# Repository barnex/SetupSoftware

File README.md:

# SetupSoftware

Software for controlling Dynamat's Magneto-Optical Scanning Microscope.

## Controller
Presents an interface to the STM32 based piezo/magnet controller with 8-channel, 16-bit bipolar ADC input.
Expected port: 5000.

## CurrentSense
An interface to a STM32 based current sensor (current through fast photodiode). 
Expected port: 5002.

## RigolInterface
Interfaces with Rigol multimeter. Expected port: 5005.

## FFTGrabber
Records samples from a soundcard and returns the Fourier transform. Expected port: 5004

Dependencies: 
  * portaudio (Ubuntu 15.04: ``sudo apt-get install portaudio19-dev``)
  * fftw (Ubuntu 15.04: ``sudo apt-get install fftw-dev``)

## HPInterface
Interfaces both with a Prologix or Arduino based GPIB controller hooked up to the HP 8672A signal generator.
Expected port: 5003 for the TX generator (excitation), 5001 for RX (detection).
Arduino-based GPIB controller firmware image: https://github.com/tibal/agipibi.

## HittiteInterface
Presumably talks to Hittite signal generator.

## Moka
java GUI for imaging with the piezo stage.

## FMRScanner
Reads ~/fmr_scanner.ini and performs FMR scan.

## Piezoscanner
Obsolete, replaced by Moka

## PiezoFMR
Obsolete.

## ScannerGUI
Obsolete, replace by Moka

## Libraries
contains certain functions and definitions that are common to all servers and even firmware. It is strongly recommended to use these, and not code your own.
TODO: makefiles

## STM32F-workarea
contains two projects: Controller firmware and CurrentSense firmware

# Protocol definition
Each server will be run by regular user, using a port specified at runtime. Use SSH tunneling for authentication and
security. Public key auth is recommended for automization.

Commands given to a server are always in ASCII, always capital letters. When (multiple) arguments are given, they are seperated by comma's.
For example, the set the position of the piezo stage halfway in each direction, the command will be (given to "Controller"):
SET,POSITION,0.5,0.5,0.5,0.0

To set the HP 8672A to 6.2GHz:
SET,FREQ,6.2e9

Physical values (frequency, current, ...) will always be handled in SI-units. Piezo position and magnet current are limited
between 0 and 1, no unit.

Each server will always reply with two int32_t values. The first holds the exit code, 1/SUCCESS if al went well. The second holds the number of bytes that will 
be returned to the user. If something went wrong, the resulting error code can be looked up in "Libraries/errors.h".
If you do not read all bytes present, they may be present in the input buffer when you read at a later point in time. After
these two bytes come the rest of the data. Returns are binary, not ASCII, unless the ID is requested.

Each server will always reply to the "ID" command with their respective identification string.

*Note: for list of command and parameters, please consult the source of the corresponding server

# Hardware

Design files for the specific electronics used for this projects are summarized in the "Hardware" folder. This may not
always be the latest version.

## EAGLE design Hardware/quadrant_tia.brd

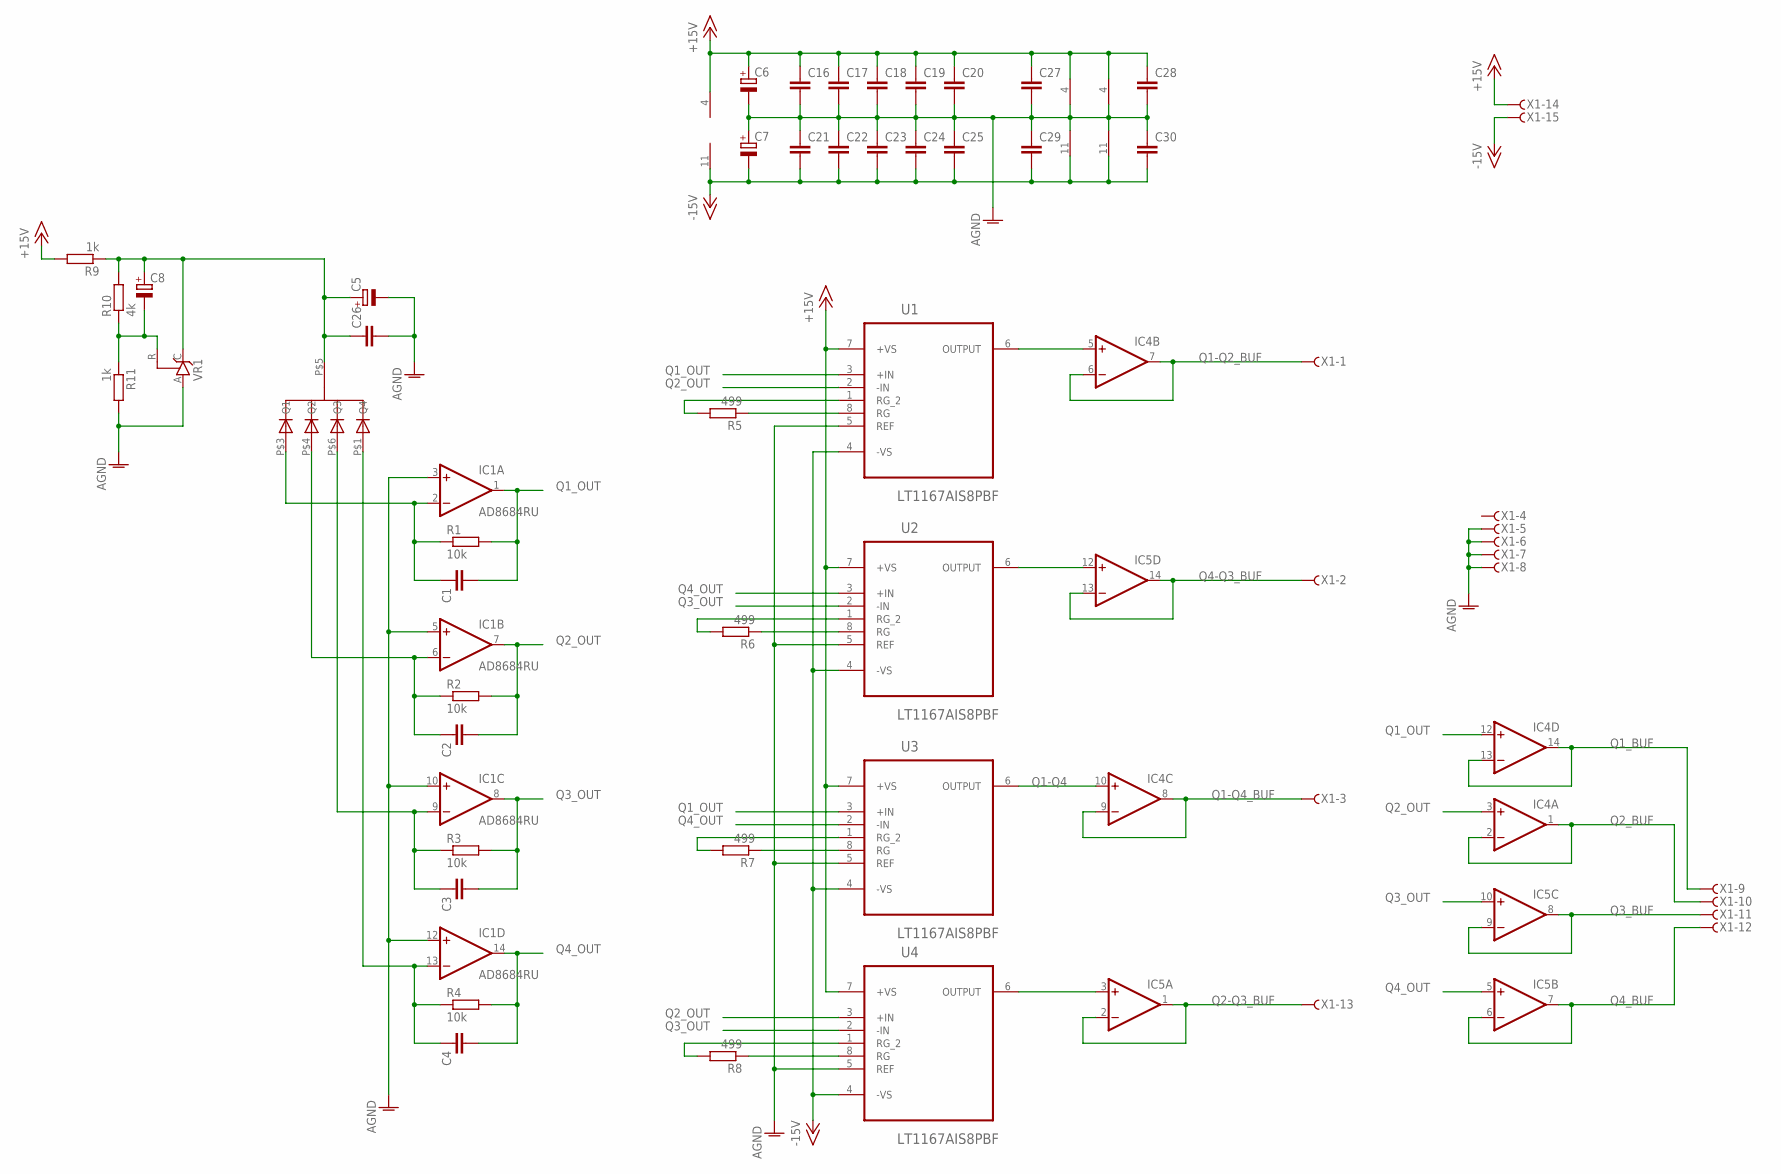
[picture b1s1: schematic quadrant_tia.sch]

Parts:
C1, C2, C3, C4, C16, C17, C18, C19, C20, C21, C22, C23, C24, C25, C26, C27, C28, C29, C30: C-EUC0805K; C0805K
C5, C6, C7, C8: CPOL-EUE5-8.5; E5-8,5
IC1: AD8684RU; TSSOP14
IC4, IC5: 4AMP_P4+11D; SO14
R1, R2, R3, R4: 10k; M1206
R5, R6, R7, R8: 499; M1206
R9, R11: 1k; R0805
R10: 4k; R0805
U1, U2, U3, U4: LT1167AIS8PBF; SOIC127P600X175-8N
U$1: QP50-6; TO-HUGE
VR1: TL431CLP; TO92-CLP
X1: F15HDHS; HDF15H

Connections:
+15V: C6.+, C16.1, C17.1, C18.1, C19.1, C20.1, C27.1, C28.1, IC1.4 (V+), IC4.4 (V+), IC5.4 (V+), R9.2, U1.7 (+VS), U2.7 (+VS), U3.7 (+VS), U4.7 (+VS), X1.14
-15V: C7.-, C21.2, C22.2, C23.2, C24.2, C25.2, C29.2, C30.2, IC1.11 (V-), IC4.11 (V-), IC5.11 (V-), U1.4 (-VS), U2.4 (-VS), U3.4 (-VS), U4.4 (-VS), X1.15
AGND: C5.-, C6.-, C7.+, C16.2, C17.2, C18.2, C19.2, C20.2, C21.1, C22.1, C23.1, C24.1, C25.1, C26.2, C27.2, C28.2, C29.1, C30.1, IC1.3 (+IN), IC1.5 (+IN), IC1.10 (+IN), IC1.12 (+IN), R11.2, U1.5 (REF), U2.5 (REF), U3.5 (REF), U4.5 (REF), VR1.A, X1.5, X1.6, X1.7, X1.8
unnamed: C1.1, IC1.2 (-IN), R1.1, U$1.P$3 (Q1)
unnamed: R7.1, U3.8 (RG)
unnamed: R7.2, U3.1 (RG_2)
unnamed: C2.1, IC1.6 (-IN), R2.1, U$1.P$4 (Q2)
unnamed: R6.1, U2.8 (RG)
unnamed: C3.1, IC1.9 (-IN), R3.1, U$1.P$6 (Q3)
unnamed: R6.2, U2.1 (RG_2)
unnamed: C4.1, IC1.13 (-IN), R4.1, U$1.P$1 (Q4)
unnamed: R5.2, U1.1 (RG_2)
unnamed: R5.1, U1.8 (RG)
unnamed: R8.2, U4.1 (RG_2)
unnamed: R8.1, U4.8 (RG)
unnamed: IC4.5 (+IN), U1.6 (OUTPUT)
unnamed: IC5.3 (+IN), U4.6 (OUTPUT)
unnamed: IC5.12 (+IN), U2.6 (OUTPUT)
unnamed: C5.+, C8.+, C26.1, R9.1, R10.2, U$1.P$5 (C), VR1.C
unnamed: C8.-, R10.1, R11.1, VR1.R
Q1-Q2_BUF: IC4.6 (-IN), IC4.7 (OUT), X1.1
Q1-Q4: IC4.10 (+IN), U3.6 (OUTPUT)
Q1-Q4_BUF: IC4.8 (OUT), IC4.9 (-IN), X1.3
Q1_BUF: IC4.13 (-IN), IC4.14 (OUT), X1.9
Q1_OUT: C1.2, IC1.1 (OUT), IC4.12 (+IN), R1.2, U1.3 (+IN), U3.3 (+IN)
Q2-Q3_BUF: IC5.1 (OUT), IC5.2 (-IN), X1.13
Q2_BUF: IC4.1 (OUT), IC4.2 (-IN), X1.10
Q2_OUT: C2.2, IC1.7 (OUT), IC4.3 (+IN), R2.2, U1.2 (-IN), U4.3 (+IN)
Q3_BUF: IC5.8 (OUT), IC5.9 (-IN), X1.11
Q3_OUT: C3.2, IC1.8 (OUT), IC5.10 (+IN), R3.2, U2.2 (-IN), U4.2 (-IN)
Q4-Q3_BUF: IC5.13 (-IN), IC5.14 (OUT), X1.2
Q4_BUF: IC5.6 (-IN), IC5.7 (OUT), X1.12
Q4_OUT: C4.2, IC1.14 (OUT), IC5.5 (+IN), R4.2, U2.3 (+IN), U3.2 (-IN)

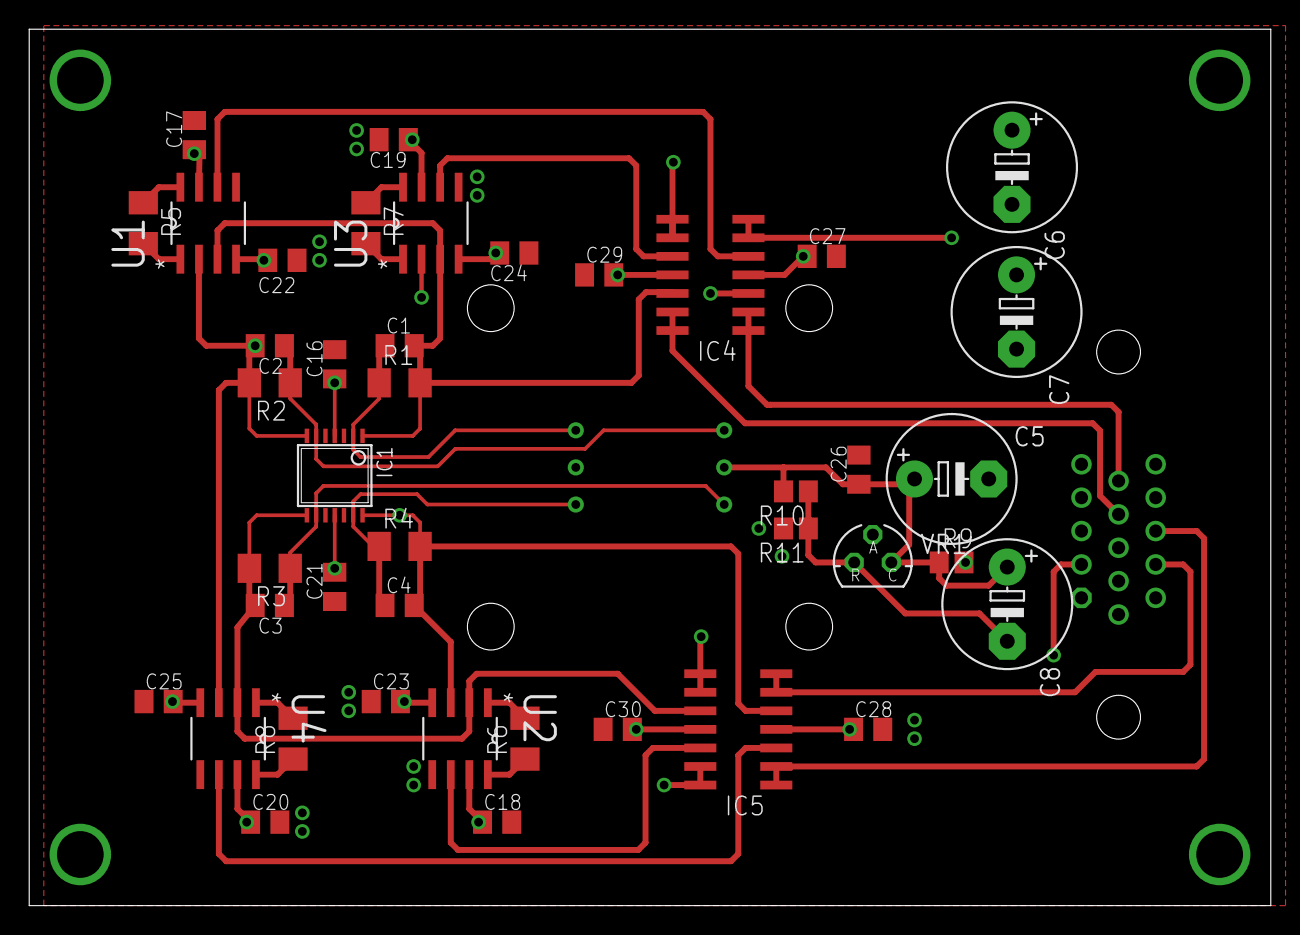
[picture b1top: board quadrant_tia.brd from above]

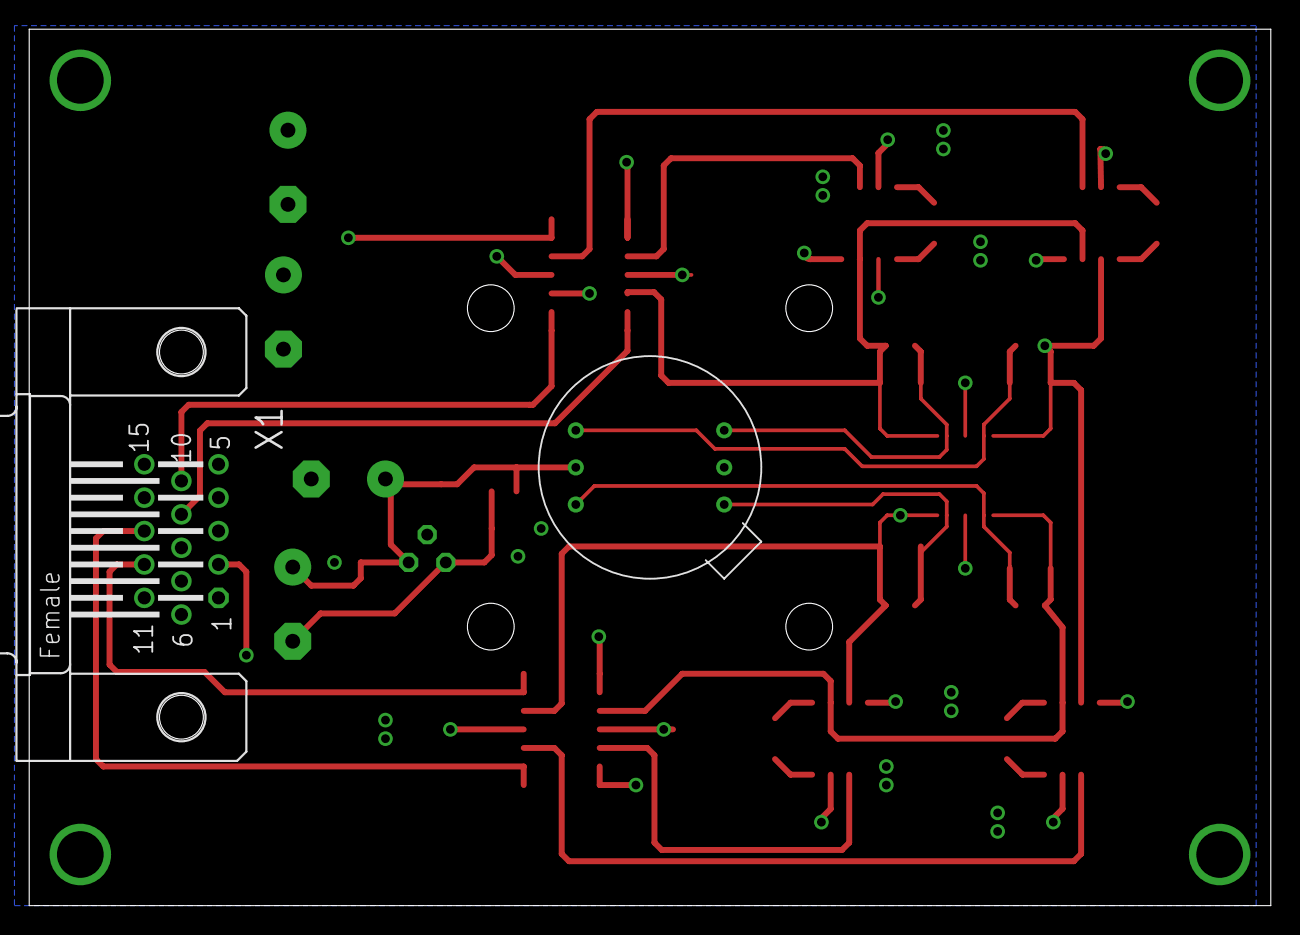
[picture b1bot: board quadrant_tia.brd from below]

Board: 4 copper layers, 85.0 x 60.0 mm, 44 parts (2 on the bottom side), 33 nets.

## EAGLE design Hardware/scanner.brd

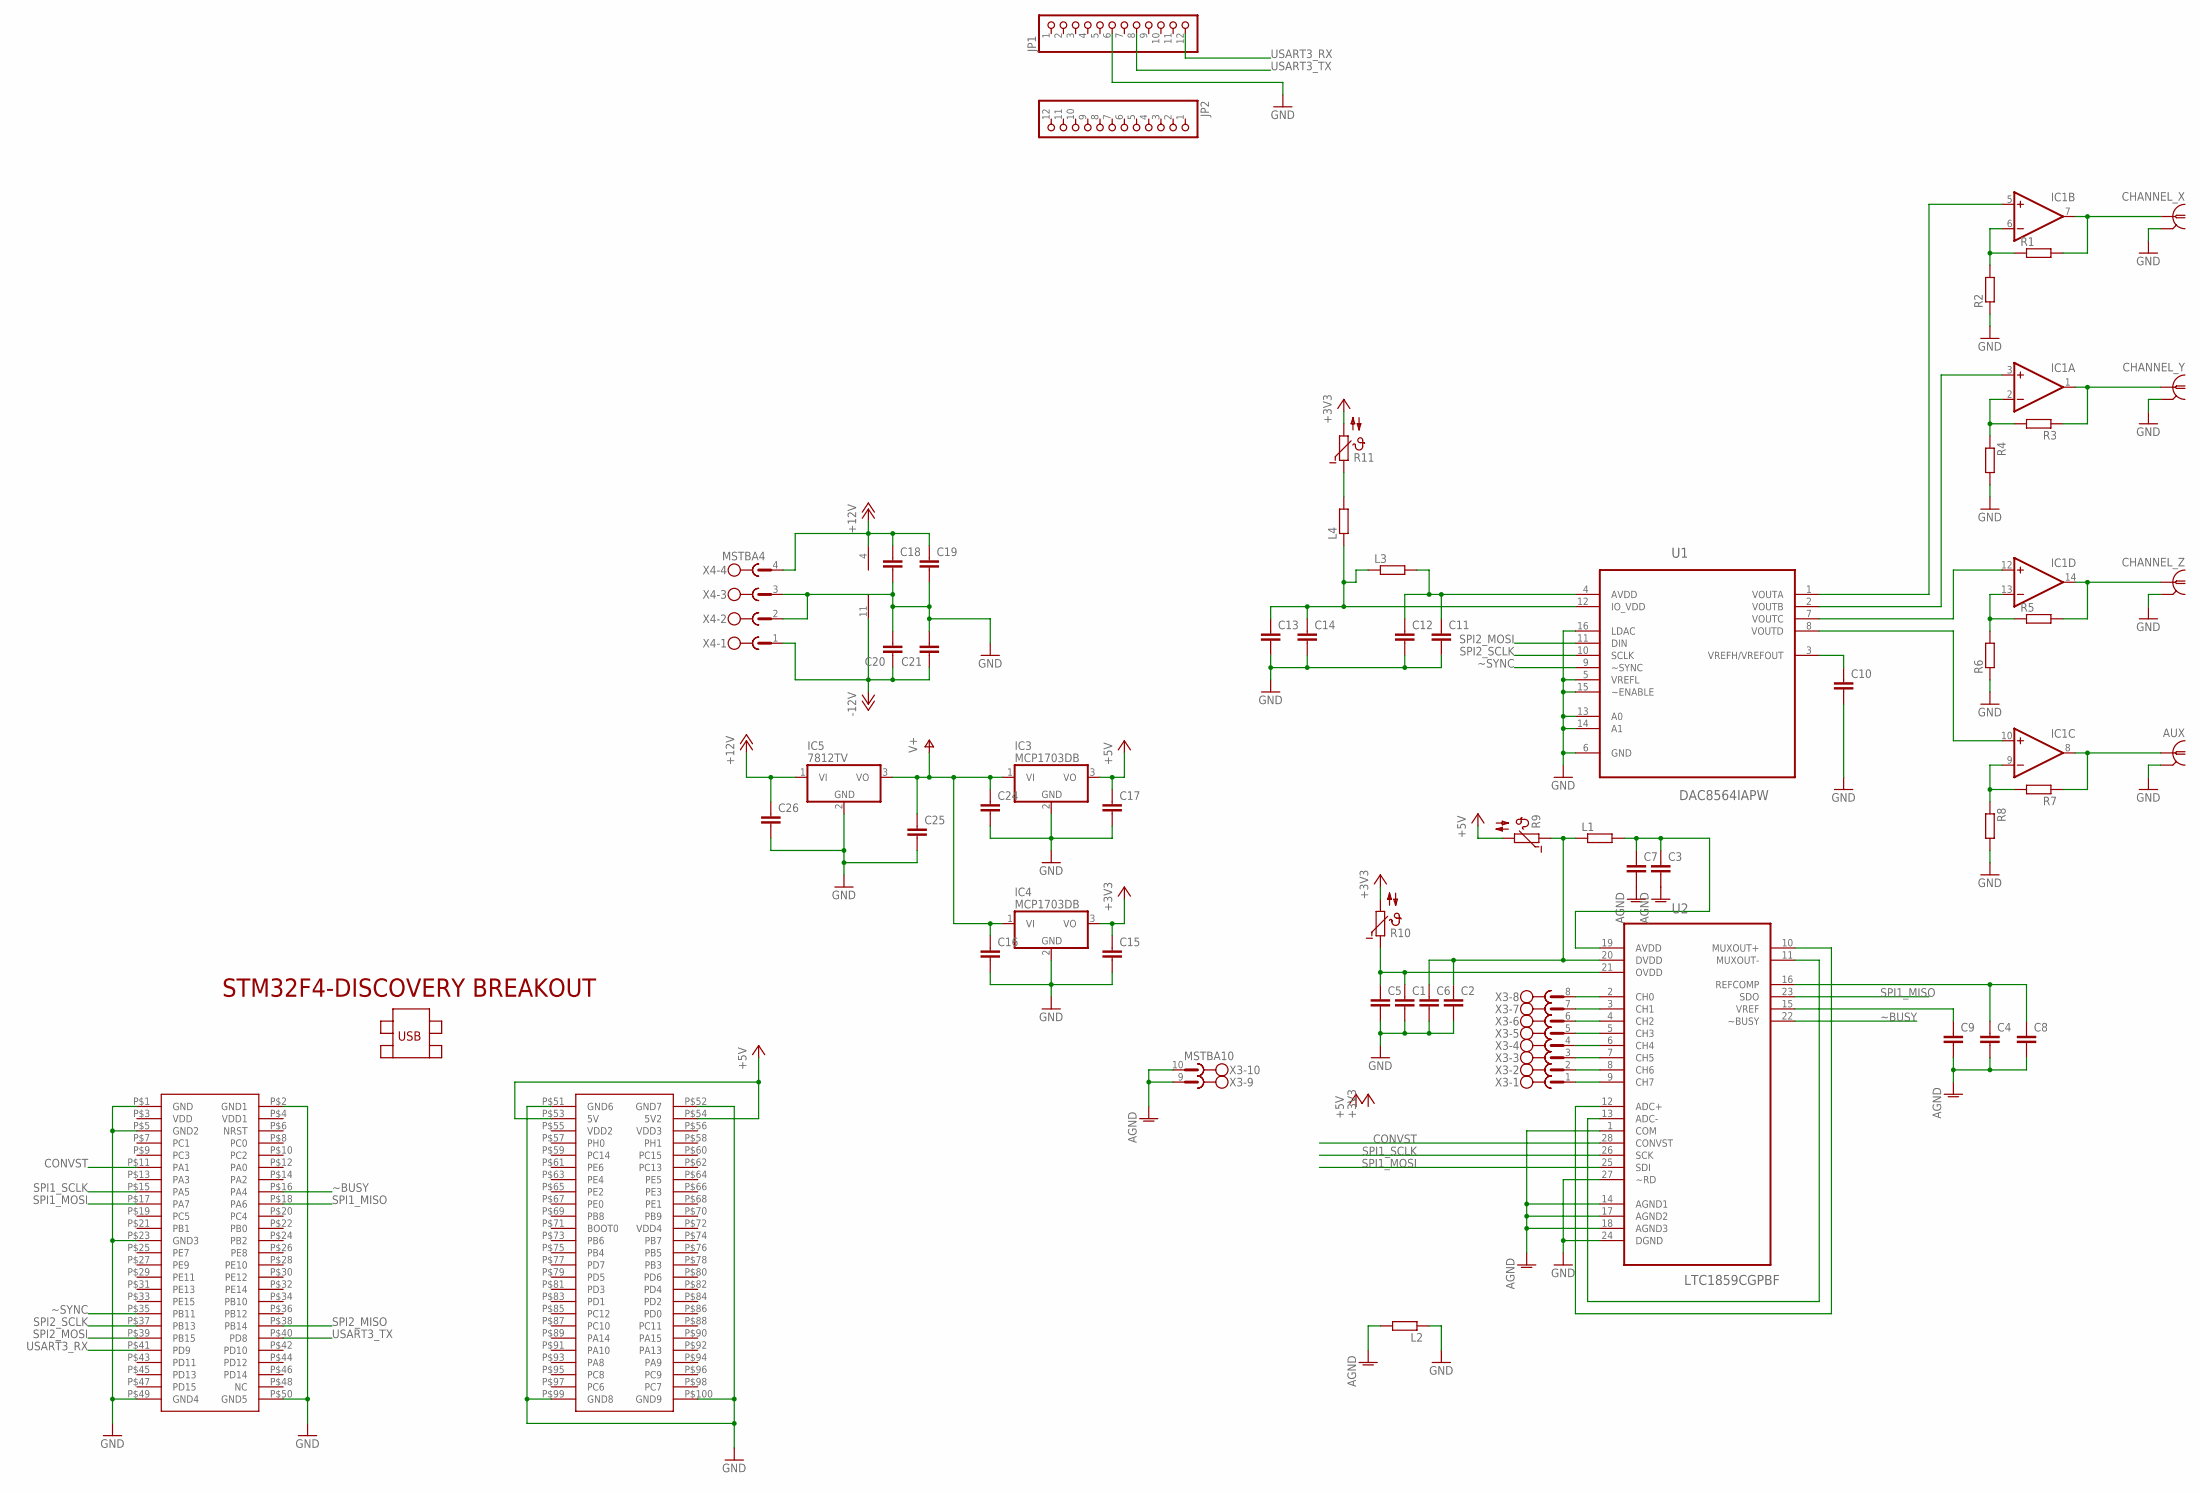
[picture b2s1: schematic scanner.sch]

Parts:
AUX: 1-227161-0; AMP_227161
C1, C2, C3, C4, C10, C11, C14, C15, C16, C17, C19, C21, C24: C-EUC0805; C0805
C5, C6, C7, C8, C9, C12, C13, C18, C20, C25, C26: C-EUC1206; C1206
CHANNEL_X: 1-227161-0; AMP_227161
CHANNEL_Y: 1-227161-0; AMP_227161
CHANNEL_Z: 1-227161-0; AMP_227161
IC1: 4AMP_P4+11D; SO14
IC3, IC4: MCP1703DB; SOT223
IC5: 7812TV; TO220V
JP1, JP2: PINHD-1X12; 1X12
L1, L2, L3, L4: R-EU_M1206; M1206
R1, R2, R3, R4, R5, R6, R7, R8: R-EU_M0805; M0805
R9, R10, R11: NTC644C; N644C
U1: DAC8564IAPW; SOP65P640X120-16N
U2: LTC1859CGPBF; SOP65P780X200-28N
U$2: STM32F4-DISCOVERY
X3: MSTBA10
X4: MSTBA4

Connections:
+3V3: C15.1, IC4.3 (VO), R10.2, R11.2
+5V: C17.1, IC3.3 (VO), R9.2, U$2.P$53 (5V), U$2.P$54 (5V2)
+12V: C18.1, C19.1, C26.1, IC1.4 (V+), IC5.1 (VI), X4.4
-12V: C20.1, C21.1, IC1.11 (V-), X4.1
AGND: C3.2, C4.2, C7.2, C8.2, C9.2, L2.2, U2.1 (COM), U2.14 (AGND1), U2.17 (AGND2), U2.18 (AGND3), X3.9, X3.10
AVCC: C3.1, C7.1, L1.2, U2.19 (AVDD)
CONVST: U2.28 (CONVST), U$2.P$11 (PA1)
GND: AUX.2, C1.2, C2.2, C5.2, C6.2, C10.2, C11.2, C12.2, C13.2, C14.2, C15.2, C16.2, C17.2, C18.2, C19.2, C20.2, C21.2, C24.2, C25.2, C26.2, CHANNEL_X.2, CHANNEL_Y.2, CHANNEL_Z.2, IC3.2 (GND), IC4.2 (GND), IC5.2 (GND), JP1.6, L2.1, R2.1, R4.2, R6.1, R8.2, U1.5 (VREFL), U1.6 (GND), U1.13 (A0), U1.14 (A1), U1.15 (~ENABLE), U1.16 (LDAC), U2.24 (DGND), U2.27 (~RD), U$2.P$1 (GND), U$2.P$2 (GND1), U$2.P$5 (GND2), U$2.P$23 (GND3), U$2.P$49 (GND4), U$2.P$50 (GND5), U$2.P$51 (GND6), U$2.P$52 (GND7), U$2.P$99 (GND8), U$2.P$100 (GND9), X4.2, X4.3
unnamed: U2.10 (MUXOUT+), U2.12 (ADC+)
unnamed: U2.11 (MUXOUT-), U2.13 (ADC-)
unnamed: IC1.5 (+IN), U1.1 (VOUTA)
unnamed: C9.1, U2.15 (VREF)
unnamed: C4.1, C8.1, U2.16 (REFCOMP)
unnamed: U2.3 (CH1), X3.7
unnamed: U2.2 (CH0), X3.8
unnamed: U2.4 (CH2), X3.6
unnamed: U2.5 (CH3), X3.5
unnamed: U2.6 (CH4), X3.4
unnamed: U2.7 (CH5), X3.3
unnamed: U2.8 (CH6), X3.2
unnamed: U2.9 (CH7), X3.1
unnamed: IC1.3 (+IN), U1.2 (VOUTB)
unnamed: IC1.12 (+IN), U1.7 (VOUTC)
unnamed: IC1.10 (+IN), U1.8 (VOUTD)
unnamed: C10.1, U1.3 (VREFH/VREFOUT)
unnamed: CHANNEL_X.1, IC1.7 (OUT), R1.2
unnamed: IC1.6 (-IN), R1.1, R2.2
unnamed: CHANNEL_Y.1, IC1.1 (OUT), R3.1
unnamed: IC1.2 (-IN), R3.2, R4.1
unnamed: C13.1, C14.1, L3.1, L4.1, U1.12 (IO_VDD)
unnamed: CHANNEL_Z.1, IC1.14 (OUT), R5.2
unnamed: IC1.13 (-IN), R5.1, R6.2
unnamed: AUX.1, IC1.8 (OUT), R7.1
unnamed: IC1.9 (-IN), R7.2, R8.1
unnamed: C11.1, C12.1, L3.2, U1.4 (AVDD)
unnamed: L4.2, R11.1
unnamed: C2.1, C6.1, L1.1, R9.1, U2.20 (DVDD)
unnamed: C1.1, C5.1, R10.1, U2.21 (OVDD)
SPI1_MISO: U2.23 (SDO), U$2.P$18 (PA6)
SPI1_MOSI: U2.25 (SDI), U$2.P$17 (PA7)
SPI1_SCLK: U2.26 (SCK), U$2.P$15 (PA5)
SPI2_MISO: U$2.P$38 (PB14)
SPI2_MOSI: U1.11 (DIN), U$2.P$39 (PB15)
SPI2_SCLK: U1.10 (SCLK), U$2.P$37 (PB13)
USART3_RX: JP1.12, U$2.P$41 (PD9)
USART3_TX: JP1.8, U$2.P$40 (PD8)
V+: C16.1, C24.1, C25.1, IC3.1 (VI), IC4.1 (VI), IC5.3 (VO)
~BUSY: U2.22 (~BUSY), U$2.P$16 (PA4)
~SYNC: U1.9 (~SYNC), U$2.P$35 (PB11)

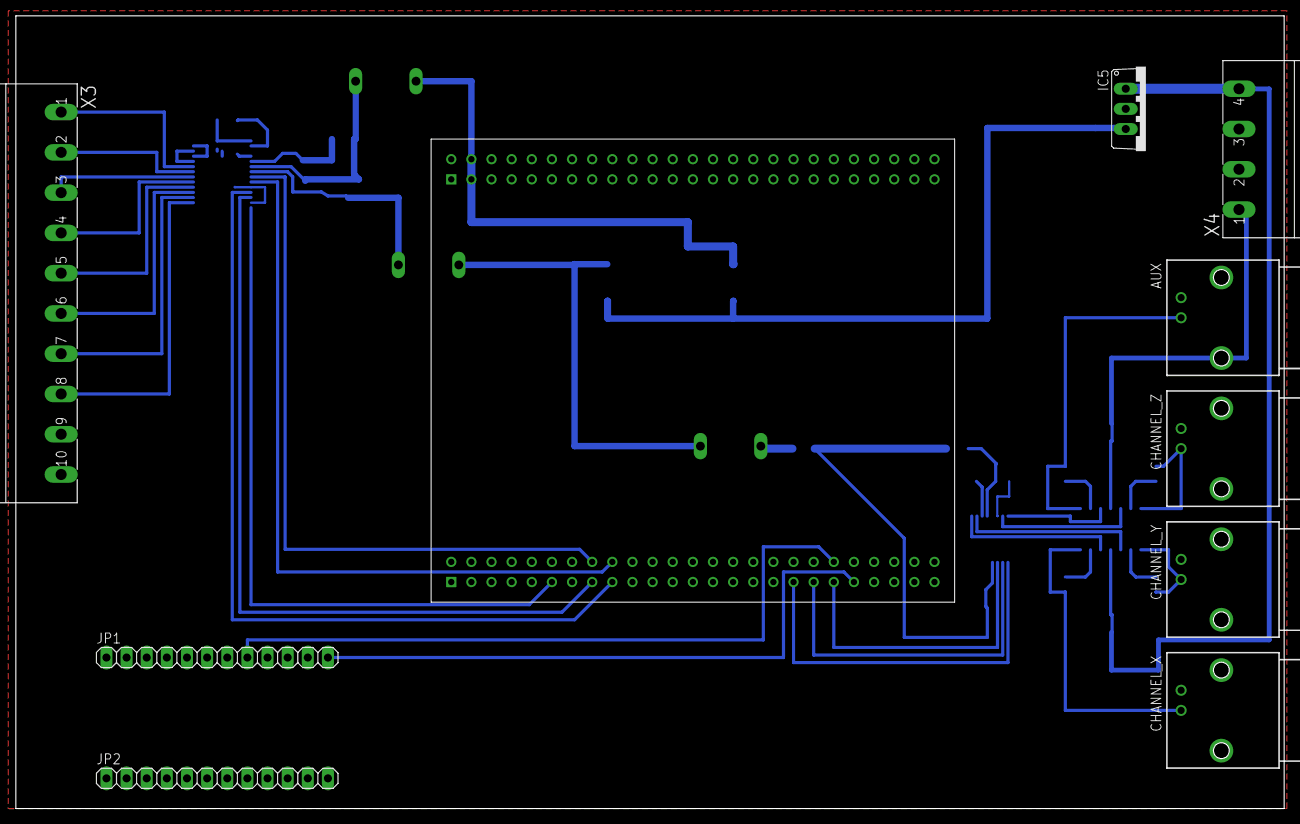
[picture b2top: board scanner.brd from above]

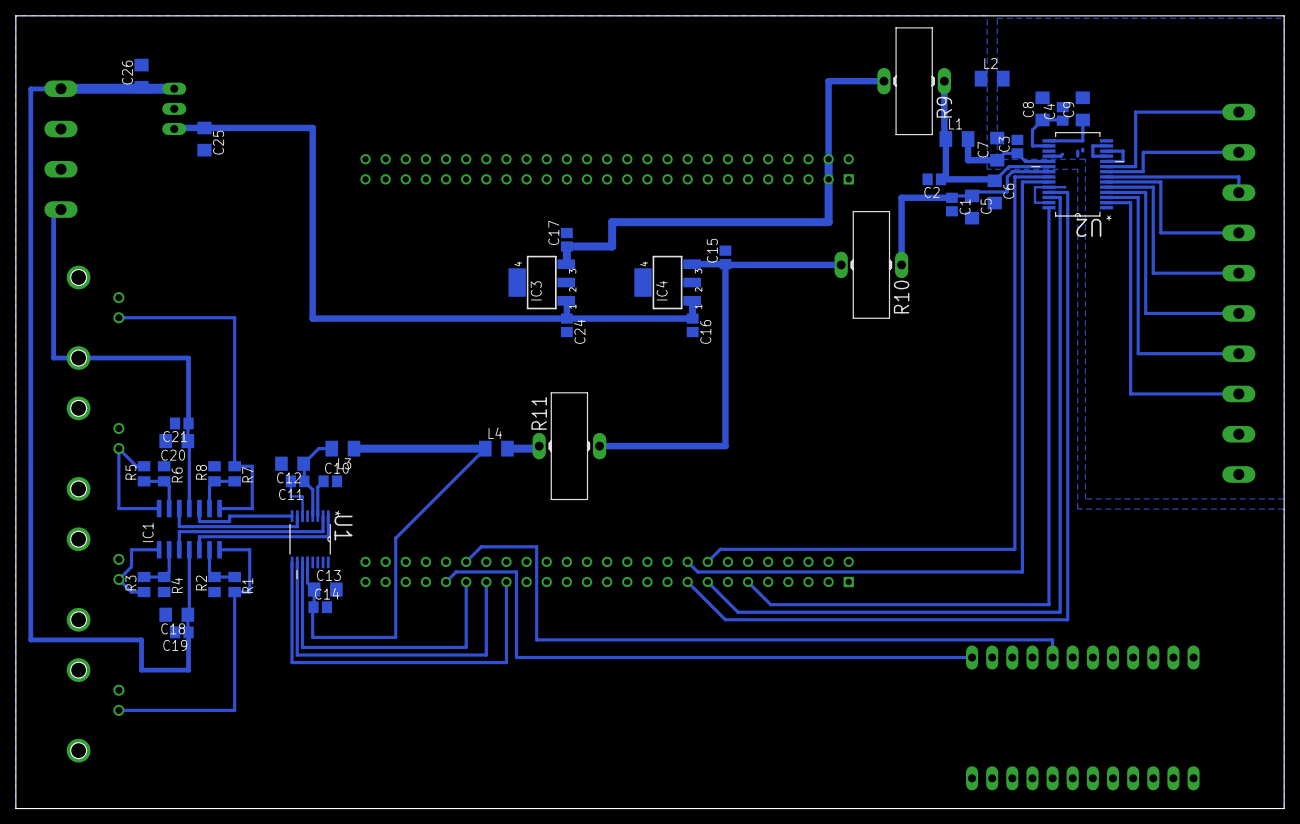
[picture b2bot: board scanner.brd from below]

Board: 2 copper layers, 160.0 x 100.0 mm, 54 parts (44 on the bottom side), 48 nets.

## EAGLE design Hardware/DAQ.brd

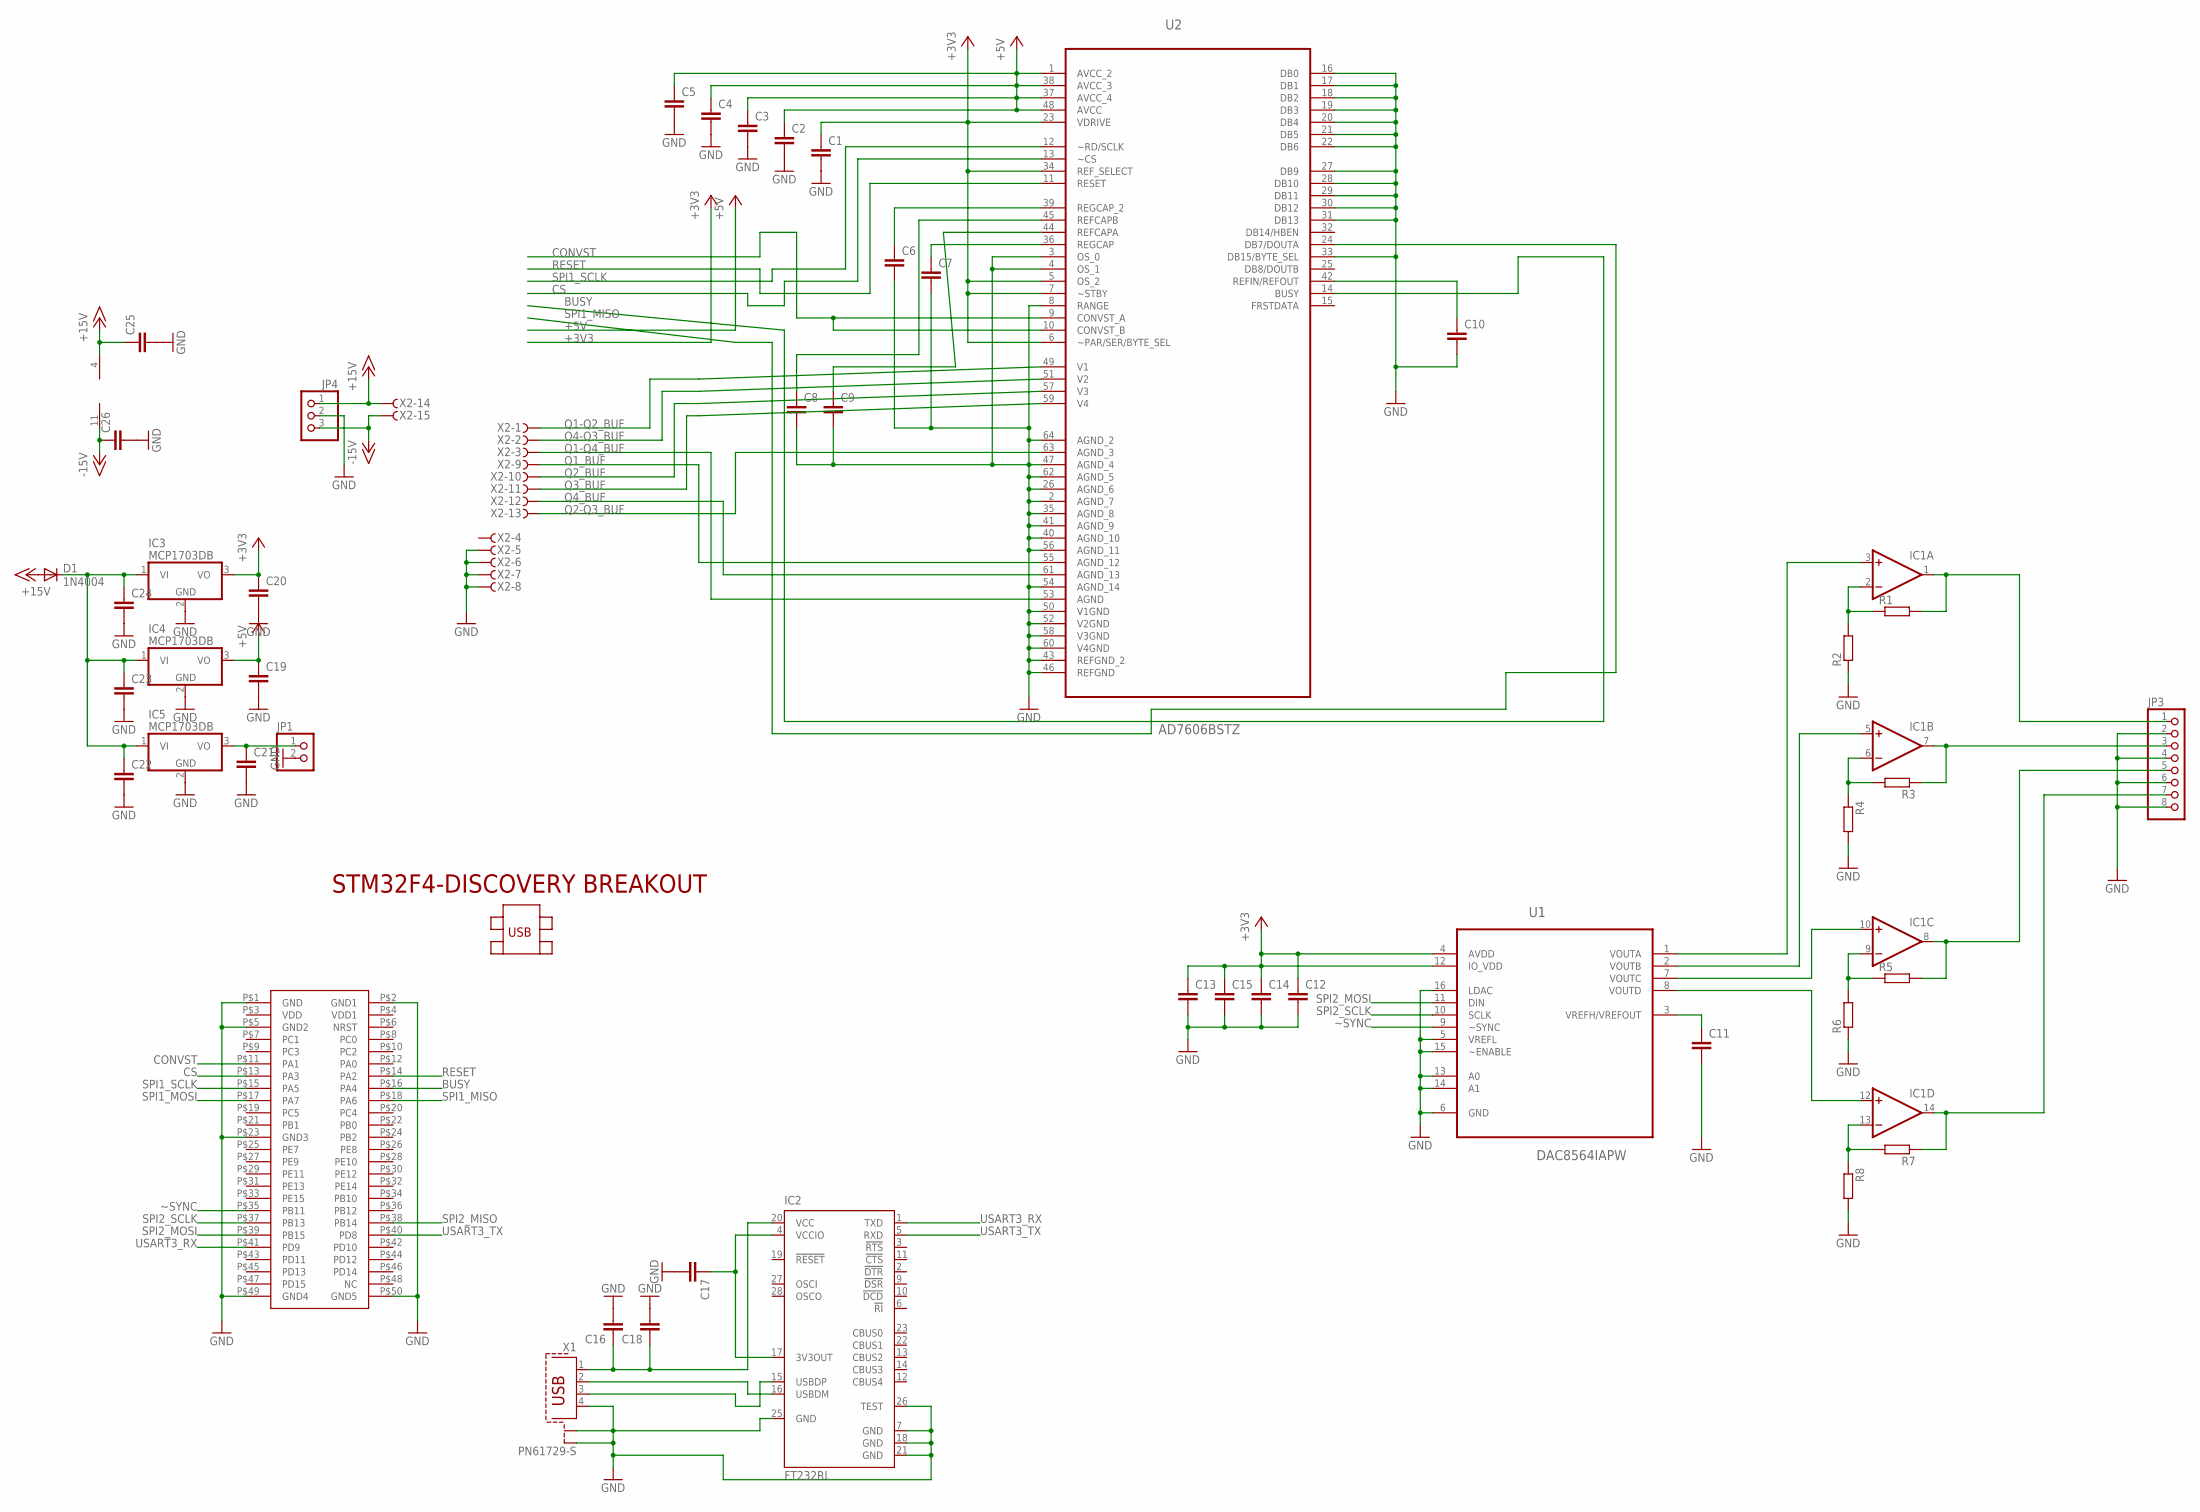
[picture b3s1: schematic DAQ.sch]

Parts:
C1, C2, C3, C4, C5, C6, C7, C11, C12, C13, C14, C15, C16, C17, C18: C-EUC0805; C0805
C8, C9, C10, C19, C20, C21, C22, C23, C24, C25, C26: C-EUC0805K; C0805K
D1: 1N4004; DO41-10
IC1: 4AMP_P4+11D; SO14
IC2: FT232RL; SSOP28
IC3, IC4, IC5: MCP1703DB; SOT223
JP1: PINHD-1X2; 1X02
JP3: PINHD-1X8; 1X08
JP4: PINHD-1X3; 1X03
R1, R2, R3, R4, R5, R6, R7, R8: R-EU_M0805; M0805
U1: DAC8564IAPW; SOP65P640X120-16N
U2: AD7606BSTZ; QFP50P1200X1200X160-64N
U$1: STM32F4-DISCOVERY
X1: PN61729-S
X2: F15HDHS; HDF15H

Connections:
+3V3: C1.1, C12.1, C13.1, C14.1, C15.1, C20.1, IC3.3 (VO), U1.4 (AVDD), U1.12 (IO_VDD), U2.5 (OS_2), U2.6 (~PAR/SER/BYTE_SEL), U2.7 (~STBY), U2.23 (VDRIVE), U2.34 (REF_SELECT)
+5V: C2.1, C3.1, C4.1, C5.1, C19.1, IC4.3 (VO), U2.1 (AVCC_2), U2.37 (AVCC_4), U2.38 (AVCC_3), U2.48 (AVCC)
+15V: C25.1, D1.A, IC1.4 (V+), JP4.1, X2.14
-15V: C26.1, IC1.11 (V-), JP4.3, X2.15
BUSY: U2.14 (BUSY), U$1.P$16 (PA4)
CONVST: U2.9 (CONVST_A), U2.10 (CONVST_B), U$1.P$11 (PA1)
CS: U2.13 (~CS), U$1.P$13 (PA3)
GND: C1.2, C2.2, C3.2, C4.2, C5.2, C6.2, C7.2, C8.2, C9.2, C10.2, C11.2, C12.2, C13.2, C14.2, C15.2, C16.2, C17.2, C18.2, C19.2, C20.2, C21.2, C22.2, C23.2, C24.2, C25.2, C26.2, IC2.7 (GND), IC2.18 (GND), IC2.21 (GND), IC2.25 (GND), IC2.26 (TEST), IC3.2 (GND), IC4.2 (GND), IC5.2 (GND), JP1.2, JP3.2, JP3.4, JP3.6, JP3.8, JP4.2, R2.1, R4.2, R6.1, R8.2, U1.5 (VREFL), U1.6 (GND), U1.13 (A0), U1.14 (A1), U1.15 (~ENABLE), U1.16 (LDAC), U2.2 (AGND_7), U2.3 (OS_0), U2.4 (OS_1), U2.8 (RANGE), U2.16 (DB0), U2.17 (DB1), U2.18 (DB2), U2.19 (DB3), U2.20 (DB4), U2.21 (DB5), U2.22 (DB6), U2.26 (AGND_6), U2.27 (DB9), U2.28 (DB10), U2.29 (DB11), U2.30 (DB12), U2.31 (DB13), U2.33 (DB15/BYTE_SEL), U2.35 (AGND_8), U2.40 (AGND_10), U2.41 (AGND_9), U2.43 (REFGND_2), U2.46 (REFGND), U2.47 (AGND_4), U2.50 (V1GND), U2.52 (V2GND), U2.54 (AGND_14), U2.56 (AGND_11), U2.58 (V3GND), U2.60 (V4GND), U2.62 (AGND_5), U2.64 (AGND_2), U$1.P$1 (GND), U$1.P$2 (GND1), U$1.P$5 (GND2), U$1.P$23 (GND3), U$1.P$49 (GND4), U$1.P$50 (GND5), X1.4, X1.S1, X1.S2, X2.5, X2.6, X2.7, X2.8
unnamed: C16.1, C18.1, IC2.20 (VCC), X1.1
unnamed: IC2.16 (USBDM), X1.2
unnamed: IC2.15 (USBDP), X1.3
unnamed: IC1.3 (+IN), U1.1 (VOUTA)
unnamed: IC1.5 (+IN), U1.2 (VOUTB)
unnamed: C7.1, U2.36 (REGCAP)
unnamed: C8.1, U2.45 (REFCAPB)
unnamed: C9.1, U2.44 (REFCAPA)
unnamed: C6.1, U2.39 (REGCAP_2)
unnamed: C17.1, IC2.4 (VCCIO), IC2.17 (3V3OUT)
unnamed: C21.1, IC5.3 (VO), JP1.1
unnamed: C10.1, U2.42 (REFIN/REFOUT)
unnamed: IC1.10 (+IN), U1.7 (VOUTC)
unnamed: IC1.12 (+IN), U1.8 (VOUTD)
unnamed: C11.1, U1.3 (VREFH/VREFOUT)
unnamed: IC1.1 (OUT), JP3.1, R1.2
unnamed: IC1.2 (-IN), R1.1, R2.2
unnamed: IC1.7 (OUT), JP3.3, R3.1
unnamed: IC1.6 (-IN), R3.2, R4.1
unnamed: IC1.8 (OUT), JP3.5, R5.2
unnamed: IC1.9 (-IN), R5.1, R6.2
unnamed: IC1.14 (OUT), JP3.7, R7.1
unnamed: IC1.13 (-IN), R7.2, R8.1
unnamed: C22.1, C23.1, C24.1, D1.C, IC3.1 (VI), IC4.1 (VI), IC5.1 (VI)
Q1-Q2_BUF: U2.49 (V1), X2.1
Q1-Q4_BUF: U2.53 (AGND), X2.3
Q1_BUF: U2.55 (AGND_12), X2.9
Q2-Q3_BUF: U2.63 (AGND_3), X2.13
Q2_BUF: U2.57 (V3), X2.10
Q3_BUF: U2.59 (V4), X2.11
Q4-Q3_BUF: U2.51 (V2), X2.2
Q4_BUF: U2.61 (AGND_13), X2.12
RESET: U2.11 (RESET), U$1.P$14 (PA2)
SPI1_MISO: U2.24 (DB7/DOUTA), U$1.P$18 (PA6)
SPI1_MOSI: U$1.P$17 (PA7)
SPI1_SCLK: U2.12 (~RD/SCLK), U$1.P$15 (PA5)
SPI2_MISO: U$1.P$38 (PB14)
SPI2_MOSI: U1.11 (DIN), U$1.P$39 (PB15)
SPI2_SCLK: U1.10 (SCLK), U$1.P$37 (PB13)
USART3_RX: IC2.1 (TXD), U$1.P$41 (PD9)
USART3_TX: IC2.5 (RXD), U$1.P$40 (PD8)
~SYNC: U1.9 (~SYNC), U$1.P$35 (PB11)

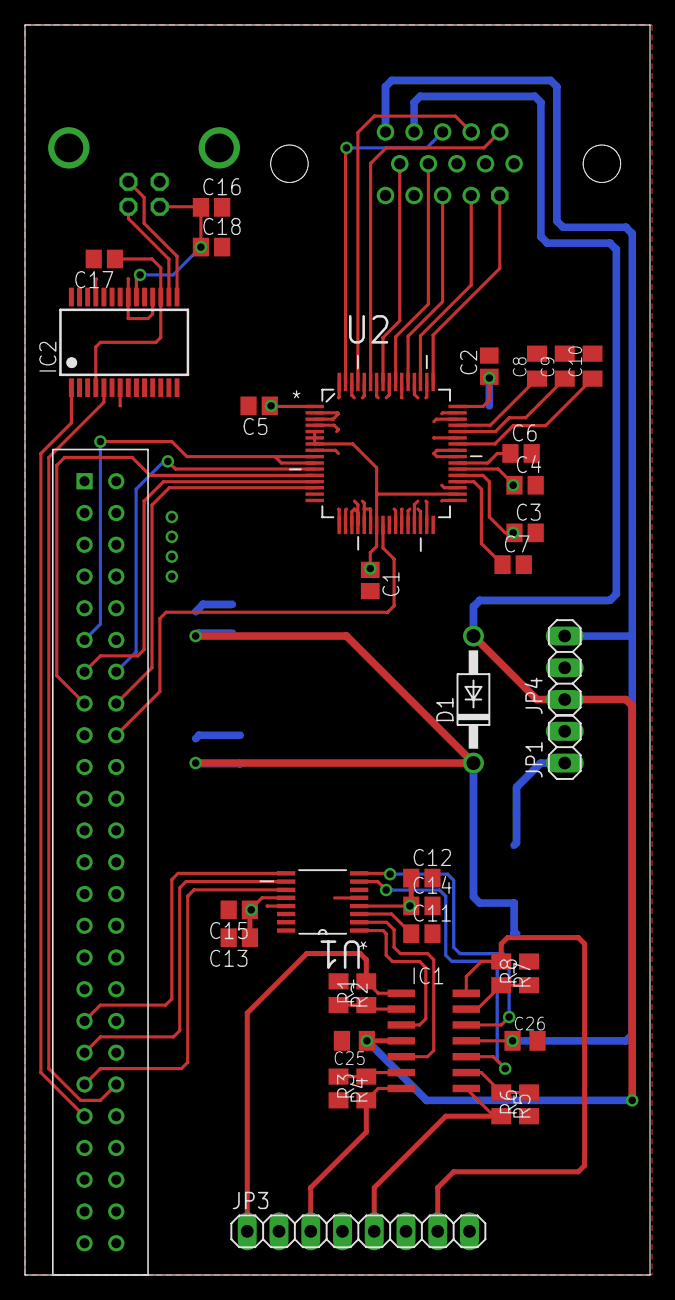
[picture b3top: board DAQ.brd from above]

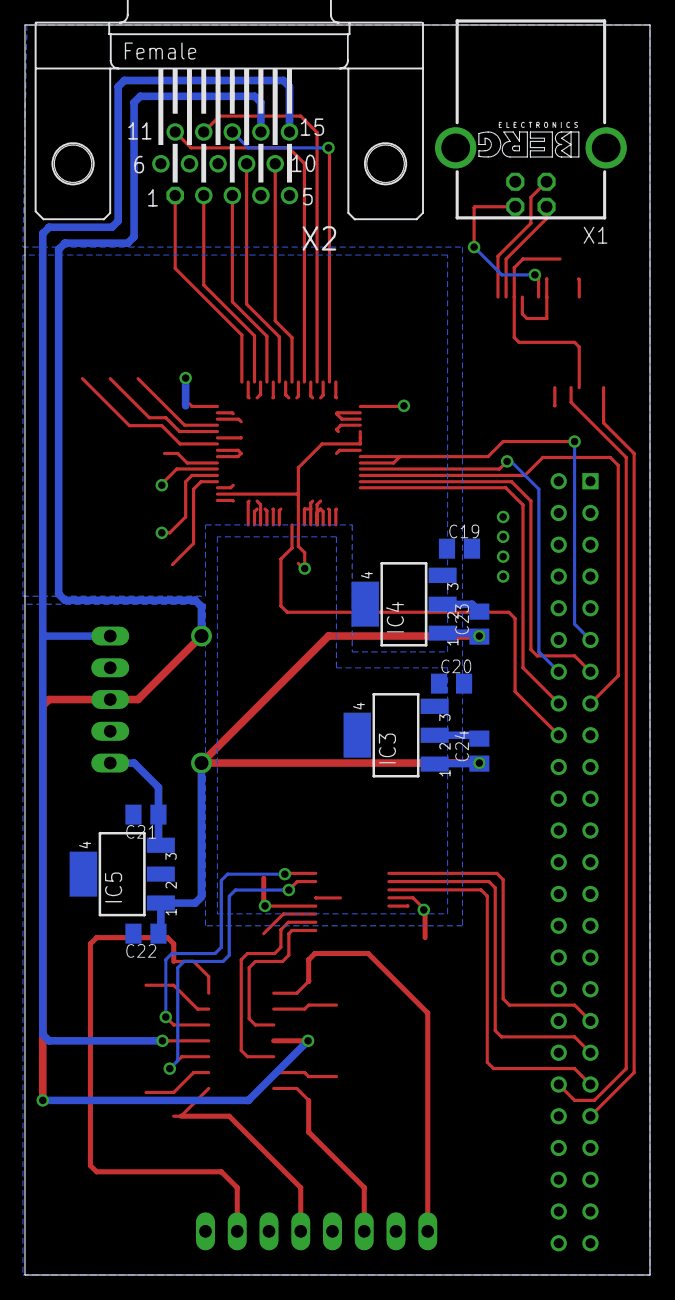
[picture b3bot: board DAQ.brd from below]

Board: 2 copper layers, 50.0 x 100.0 mm, 48 parts (11 on the bottom side), 48 nets.
